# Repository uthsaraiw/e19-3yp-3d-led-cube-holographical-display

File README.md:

<div align = "center">
  <image src="https://github.com/cepdnaclk/e19-3yp-3d-led-cube-holographical-display/blob/main/docs/images/logo-ex.png" alt ="">
  <h1 align="center">3D LED CUBE HOLOGRAPHIC DISPLAY</h1>
</div>

___

## Introduction

Experience the future of interactive entertainment with our 3D LED Holographic Display. This innovative device goes beyond traditional displays, offering users the ability to showcase 3D Objects, Engaging Animations and Simple Games. Users can join our collaborative platform and connect, share their creativity, and get inspired by others. Users hold the reins, deciding how to wield the cube's versatile display.

## Features
Unlock the potential of our 3D LED holographic display with these standout features:

- Effortlessly showcase your chosen 3D object files, transforming them into captivating visual experiences.
- Bring your content to life with the ability to play simple animations.
- Immerse yourself in inbuilt interactive games for a dynamic and engaging experience.
- Enjoy seamless touch control for intuitive navigation.
- Stay connected globally—our display is cloud-enabled, allowing you to control it from anywhere in the world.

## Usage

- <b>Interactive entertainment device with exchange Hub:</b>  Basically, an interactive entertainment device which comes with touch control. Users can engage with our collaborative platform, sharing 3D files, animations, and Cube tips. Inspire and be inspired by diverse use cases, fostering a dynamic community of creativity.
- <b>Versatile Social Impact:</b>  Elevate gatherings, interiors, logos, and events dynamically with mesmerizing displays. Let the device transform social settings with its captivating and interactive features.
- <b>Resolution Beyond Entertainment:</b> Unleash the device's potential with improved resolution for product showcases, enriched education experiences, and advanced scientific visualizations. Explore a world beyond conventional entertainment possibilities.

Simply, user can get creative and define their usage of the cube.

___

### Contributors 
- <a href = "https://github.com/Bambara123">Kavindu Bambaragama</a>
- <a href = "https://github.com/Madhushanka00">Mahesha Madhushanka</a>
- <a href = "https://github.com/DhinushikaAbrew">Dhinushika Abrew</a>
- <a href = "https://github.com/uthsaraiw">Uthsara Wickramaarachchi</a>
- <a href = "https://github.com/Bambara123">Sapuni Witharana</a>

<p>Check our <a href = "https://cepdnaclk.github.io/e19-3yp-3d-led-cube-holographical-display/"> project page</a> here.</p>

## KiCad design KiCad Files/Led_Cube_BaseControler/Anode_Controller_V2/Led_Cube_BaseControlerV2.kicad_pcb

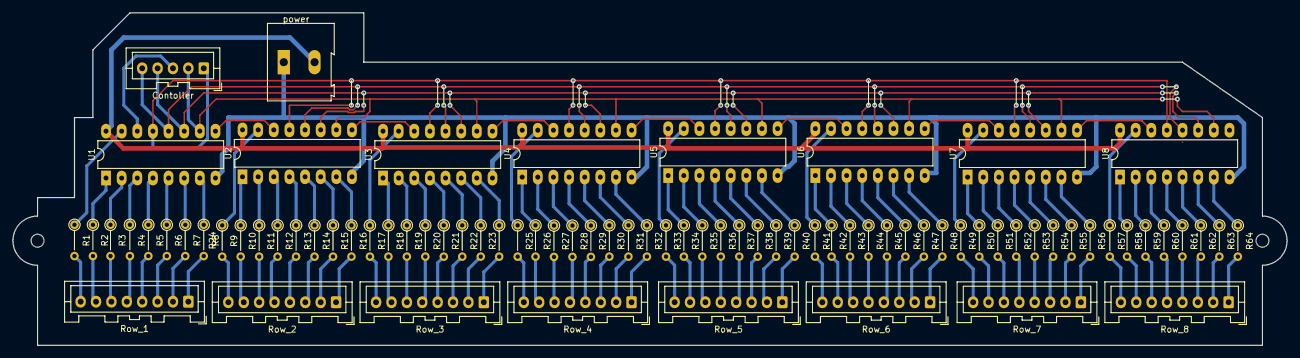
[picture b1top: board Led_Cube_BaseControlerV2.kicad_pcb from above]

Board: 2 copper layers, 207.0 x 54.0 mm, 82 parts (0 on the bottom side), 142 nets.

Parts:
Contoller: RPi Controller; JST_XA_B05B-XASK-1_1x05_P2.50mm_Vertical
R1, R2, R3, R4, R5, R6, R7, R8, R9, R10, R11, R12, R13, R14, R15, R16, R17, R18, R19, R20, R21, R22, R23, R24, R25, R26, R27, R28, R29, R30, R31, R32, R33, R34, R35, R36, R37, R38, R39, R40, R41, R42, R43, R44, R45, R46, R47, R48, R49, R50, R51, R52, R53, R54, R55, R56, R57, R58, R59, R60, R61, R62, R63, R64: R_Small; R_Axial_DIN0204_L3.6mm_D1.6mm_P5.08mm_Vertical
Row_1: Row_01; JST_XA_B08B-XASK-1_1x08_P2.50mm_Vertical
Row_2: Row_02; JST_XA_B08B-XASK-1_1x08_P2.50mm_Vertical
Row_3: Row_03; JST_XA_B08B-XASK-1_1x08_P2.50mm_Vertical
Row_4: Row_04; JST_XA_B08B-XASK-1_1x08_P2.50mm_Vertical
Row_5: Row_05; JST_XA_B08B-XASK-1_1x08_P2.50mm_Vertical
Row_6: Row_06; JST_XA_B08B-XASK-1_1x08_P2.50mm_Vertical
Row_7: Row_07; JST_XA_B08B-XASK-1_1x08_P2.50mm_Vertical
Row_8: Row_08; JST_XA_B08B-XASK-1_1x08_P2.50mm_Vertical
U1, U2, U3, U4, U5, U6, U7, U8: 74HC595; DIP-16_W7.62mm_LongPads
power: Power; TerminalBlock_Altech_AK300-2_P5.00mm

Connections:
unnamed: Contoller.1, U1.13 (~OE), U2.13 (~OE), U3.13 (~OE), U4.13 (~OE), U5.13 (~OE), U6.13 (~OE), U7.13 (~OE), U8.13 (~OE)
unnamed: Contoller.2, U1.10 (~SRCLR), U2.10 (~SRCLR), U3.10 (~SRCLR), U4.10 (~SRCLR), U5.10 (~SRCLR), U6.10 (~SRCLR), U7.10 (~SRCLR), U8.10 (~SRCLR)
unnamed: Contoller.3, U1.14 (SER)
unnamed: Contoller.4, U1.11 (SRCLK), U2.11 (SRCLK), U3.11 (SRCLK), U4.11 (SRCLK), U5.11 (SRCLK), U6.11 (SRCLK), U7.11 (SRCLK), U8.11 (SRCLK)
unnamed: Contoller.5, U1.12 (RCLK), U2.12 (RCLK), U3.12 (RCLK), U4.12 (RCLK), U5.12 (RCLK), U6.12 (RCLK), U7.12 (RCLK), U8.12 (RCLK)
unnamed: U1.8 (GND), U2.8 (GND), U3.8 (GND), U4.8 (GND), U5.8 (GND), U6.8 (GND), U7.8 (GND), U8.8 (GND), power.1
unnamed: U1.16 (VCC), U2.16 (VCC), U3.16 (VCC), U4.16 (VCC), U5.16 (VCC), U6.16 (VCC), U7.16 (VCC), U8.16 (VCC), power.2
unnamed: R8.2, Row_1.1
unnamed: R7.2, Row_1.2
unnamed: R6.2, Row_1.3
unnamed: R5.2, Row_1.4
unnamed: R4.2, Row_1.5
unnamed: R3.2, Row_1.6
unnamed: R2.2, Row_1.7
unnamed: R1.2, Row_1.8
unnamed: R16.2, Row_2.1
unnamed: R15.2, Row_2.2
unnamed: R14.2, Row_2.3
unnamed: R13.2, Row_2.4
unnamed: R12.2, Row_2.5
unnamed: R11.2, Row_2.6
unnamed: R10.2, Row_2.7
unnamed: R9.2, Row_2.8
unnamed: R24.2, Row_3.1
unnamed: R23.2, Row_3.2
unnamed: R22.2, Row_3.3
unnamed: R21.2, Row_3.4
unnamed: R20.2, Row_3.5
unnamed: R19.2, Row_3.6
unnamed: R18.2, Row_3.7
unnamed: R17.2, Row_3.8
unnamed: R32.2, Row_4.1
unnamed: R31.2, Row_4.2
unnamed: R30.2, Row_4.3
unnamed: R29.2, Row_4.4
unnamed: R28.2, Row_4.5
unnamed: R27.2, Row_4.6
unnamed: R26.2, Row_4.7
unnamed: R25.2, Row_4.8
unnamed: R40.2, Row_5.1
unnamed: R39.2, Row_5.2
unnamed: R38.2, Row_5.3
unnamed: R37.2, Row_5.4
unnamed: R36.2, Row_5.5
unnamed: R35.2, Row_5.6
unnamed: R34.2, Row_5.7
unnamed: R33.2, Row_5.8
unnamed: R48.2, Row_6.1
unnamed: R47.2, Row_6.2
unnamed: R46.2, Row_6.3
unnamed: R45.2, Row_6.4
unnamed: R44.2, Row_6.5
unnamed: R43.2, Row_6.6
unnamed: R42.2, Row_6.7
unnamed: R41.2, Row_6.8
unnamed: R56.2, Row_7.1
unnamed: R55.2, Row_7.2
unnamed: R54.2, Row_7.3
unnamed: R53.2, Row_7.4
unnamed: R52.2, Row_7.5
unnamed: R51.2, Row_7.6
unnamed: R50.2, Row_7.7
unnamed: R49.2, Row_7.8
unnamed: R64.2, Row_8.1
unnamed: R63.2, Row_8.2
unnamed: R62.2, Row_8.3
unnamed: R61.2, Row_8.4
unnamed: R60.2, Row_8.5
unnamed: R59.2, Row_8.6
unnamed: R58.2, Row_8.7
unnamed: R57.2, Row_8.8
unnamed: R9.1, U2.15 (QA)
unnamed: R10.1, U2.1 (QB)
unnamed: R11.1, U2.2 (QC)
unnamed: R12.1, U2.3 (QD)
unnamed: R13.1, U2.4 (QE)
unnamed: R14.1, U2.5 (QF)
unnamed: R15.1, U2.6 (QG)
unnamed: U2.9 (QH'), U3.14 (SER)
unnamed: R16.1, U2.7 (QH)
unnamed: U1.9 (QH'), U2.14 (SER)
unnamed: R17.1, U3.15 (QA)
unnamed: R18.1, U3.1 (QB)
unnamed: R19.1, U3.2 (QC)
unnamed: R20.1, U3.3 (QD)
unnamed: R21.1, U3.4 (QE)
unnamed: R22.1, U3.5 (QF)
unnamed: R23.1, U3.6 (QG)
unnamed: U3.9 (QH'), U4.14 (SER)
unnamed: R24.1, U3.7 (QH)
unnamed: R1.1, U1.15 (QA)
unnamed: R2.1, U1.1 (QB)
unnamed: R3.1, U1.2 (QC)
unnamed: R4.1, U1.3 (QD)
unnamed: R5.1, U1.4 (QE)
unnamed: R6.1, U1.5 (QF)
unnamed: R7.1, U1.6 (QG)
unnamed: R8.1, U1.7 (QH)
unnamed: R25.1, U4.15 (QA)
unnamed: R26.1, U4.1 (QB)
unnamed: R27.1, U4.2 (QC)
unnamed: R28.1, U4.3 (QD)
unnamed: R29.1, U4.4 (QE)
unnamed: R30.1, U4.5 (QF)
unnamed: R31.1, U4.6 (QG)
unnamed: U4.9 (QH'), U5.14 (SER)
unnamed: R32.1, U4.7 (QH)
unnamed: R33.1, U5.15 (QA)
unnamed: R34.1, U5.1 (QB)
unnamed: R35.1, U5.2 (QC)
unnamed: R36.1, U5.3 (QD)
unnamed: R37.1, U5.4 (QE)
unnamed: R38.1, U5.5 (QF)
unnamed: R39.1, U5.6 (QG)
unnamed: U5.9 (QH'), U6.14 (SER)
unnamed: R40.1, U5.7 (QH)
unnamed: R41.1, U6.15 (QA)
unnamed: R42.1, U6.1 (QB)
unnamed: R43.1, U6.2 (QC)
unnamed: R44.1, U6.3 (QD)
unnamed: R45.1, U6.4 (QE)
unnamed: R46.1, U6.5 (QF)
unnamed: R47.1, U6.6 (QG)
unnamed: U6.9 (QH'), U7.14 (SER)
unnamed: R48.1, U6.7 (QH)
unnamed: R49.1, U7.15 (QA)
unnamed: R50.1, U7.1 (QB)
unnamed: R51.1, U7.2 (QC)
unnamed: R52.1, U7.3 (QD)
unnamed: R53.1, U7.4 (QE)
unnamed: R54.1, U7.5 (QF)
unnamed: R55.1, U7.6 (QG)
unnamed: U7.9 (QH'), U8.14 (SER)
unnamed: R56.1, U7.7 (QH)
unnamed: R57.1, U8.15 (QA)
unnamed: R58.1, U8.1 (QB)
unnamed: R59.1, U8.2 (QC)
unnamed: R60.1, U8.3 (QD)
unnamed: R61.1, U8.4 (QE)
unnamed: R62.1, U8.5 (QF)
unnamed: R63.1, U8.6 (QG)
unnamed: R64.1, U8.7 (QH)

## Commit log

2023-11-30 Creared PlatformIO Project file for Hardware testing
2023-12-01 Example code file fod 8x8 LED matrix
2023-12-04 added shift register testing sketches
2023-12-04 comment about the code
2023-12-06 Added shift register testing files
    Here I used 2 of 72HC595 8 bit shift registers. The folder includes sketch file (.ino) and circuit diagram (.png) and the schematic view of the circuit (.pdf).
    Thinking about connect 32 registers in series for control 16x16 single led layer.
2023-12-08 New react app started.
2023-12-08 Added 8x8 controller module KiCad files, and igbr files
2023-12-08 feed and right bar added.
2023-12-09 UI design files added.
2023-12-09 Home page development started.
2023-12-09 Front end updated
2023-12-10 Testing files of 4x4x4 prototype cube and PCB .zip files
2023-12-10 The python file that mapping the .obj file's information into the grid is commited along with some .obj files
2023-12-12 Project page is updated
2023-12-13 video added.
2023-12-19 pcb design new versions, request letters
2023-12-26 new Kicad files and circuits Uploaded
2023-12-31 app buttons updated
2024-01-02 Parellel processing testing files and New circuit designes uploaded
2024-01-03 Update README.md
    added uthsaraiw profile for github readme
2024-01-03 Update README.md
    the names of the contributors are updated
2024-01-03 backend start
2024-01-04 most of ui's done without functions
2024-01-04 update backend
2024-01-04 backend login function
2024-01-04 Functions updated: main routing, first login API request. sent data to API endpoint.
2024-01-05 Routing done
2024-01-05 backend security part update
2024-01-05 Now we can send data into endpoints : register, login, upload object, make post.
2024-01-05 backend update
2024-01-05 test
2024-01-05 update register part
2024-01-06 now you can login and register using UI.
2024-01-06 objectfile upload
2024-01-07 update object file uploading
2024-01-07 just test files added
2024-01-07 object file uploading part
2024-01-07 the file that sent to api endpoint will be saved in uploads folder.
2024-01-07 hello
2024-01-07 pick file
2024-01-08 susi's code working
2024-01-08 Updated the python code file and add try and catch errors.
2024-01-08 get the hex file from database
2024-01-08 hex file upload
2024-01-08 Updated to create a hex file.
2024-01-08 hex file updates on the database
2024-01-08 now can get object file
2024-01-08 now each user email can create one object inside nodejs environment, and when he update new objects , that will be replaced. anyway you can retrieve all the .hex files from the database because each 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
2024-01-09 email comes to the upload page
2024-01-09 Updated the project page.
2024-01-09 last object
2024-01-09 last commit
2024-01-09 toaste messages added
2024-01-09 Added a video link to the project page.
2024-01-14 post part update
2024-01-14 change
2024-01-14 file post part update
2024-01-18 post retrieval using fake url end point is done.
2024-01-19 updated files
2024-01-22 news feed can be updated according to the data derived from the db.
2024-01-22 post files
2024-01-23 getpost
2024-01-23 upload a file done, may have problems when uploading multiple files. user page update done, feed update done.
2024-01-24 Multiple images can be sent for the backend. I have commented some part in object in Object file route please check.
2024-01-24 object uploading perfectly working
2024-01-24 modify post part
2024-01-24 can get data for feed and can upload posts
2024-01-26 settings, comment, react page done - waiting for backend.
2024-01-26 react part update
2024-01-26 now we are responsive
2024-01-27 navigation for different routes done, we can identify where we are in using passed props.
2024-01-27 comment part update
2024-01-27 Section dividing code was added.
2024-01-27 user profile upload part
2024-01-27 add followers
2024-01-27 Object can be previewed before send
2024-01-27 get user data
2024-01-27 put caption and date in post
2024-01-28 reacting and commenting updated
2024-01-28 additional script.py added
2024-01-28 code and object download , share post
2024-01-28 following part update
2024-01-28 Final Raspberry pi scripts Upto 28/01
2024-01-28 can follow, but cannot unfollow.
2024-01-29 comments updates instantly
2024-02-02 Create gitattributes
2024-02-02 Adding flutter app Holo Cube
    No other changes made; only the flutter app is added to the repo; this contains the fully up to date flutter files
